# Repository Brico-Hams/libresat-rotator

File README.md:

<p align="center"><a href="https://bricohams.org">bricohams.org</a> · Anatol EA5KAO · Diego EA5JEF · Pedro Roca Molina</p>

# BricoHams · LibreSat rotators (LSR-1 and LSR-2)

**Light, cheap, open az/el rotators for amateur satellites.** Authors: Anatol EA5KAO, Diego EA5JEF, Pedro Roca Molina.

| | LSR-1 (portable) | LSR-2 (fixed station, heavy) |
|---|---|---|
| Design | printed cycloid actuators, Pi head, tripod or backpack | **replica of the SARCNET SARCTrac Mk4** (MIT files in [`third_party/sarctrac-mk4`](third_party/sarctrac-mk4)) |
| Drive | 2 × printed cycloid 25:1 + NEMA17 | 2 × NMRV30 worm gearbox 50:1 + NEMA23 23HS32-4004S, DM542T drivers at 48 V |
| Mass / cost | ≈ 2.3 kg, ≈ 150 € ([BOM](docs/BOM.md)) | **≈ 15.9 kg, ≈ 900 € (est.)**, generated by `calc/lsr2_mk4_bom.py` ([BOM_LSR2](docs/BOM_LSR2.md)) |
| Range | AZ 0–450°, EL 0–180° (flip) | AZ ±360° (cable wrap), EL −30…150° |
| Speed / load | pass planner < 16°/s | 12°/s; wind, gravity and speed limits in [LSR2_SIZING](docs/LSR2_SIZING.md) |
| Accuracy target | < 0.1° after calibration ([CALIBRATION](docs/CALIBRATION.md)) | same target, acceptance in [LSR2_ACCEPTANCE](docs/LSR2_ACCEPTANCE.md) |

**Build pipeline:** `make calc` (engineering checks and generated docs) · `make lsr2` (LSR-2 CAD, STL, laser DXF, drawings, wiring, BOM, technical figures) · `make render` (photoreal renders with Blender) · `make test` (firmware host tests and software tests).

**Credits:** SARCNET (SARCTrac Mk4 FreeCAD files under the MIT licence, the base of LSR-2; Mk5 published data; ideas from MK1), [SatNOGS Rotator v3](https://gitlab.com/librespacefoundation/satnogs/satnogs-rotator), [AntRunner](https://github.com/wuxx/AntRunner), [Sweep Dynamics](https://www.sweepdynamics.com/). Licences are listed in [Licences](#licences). Branding: [docs/BRANDING.md](docs/BRANDING.md).

---

## LSR-1: portable rotator

**A light, cheap, open az/el rotator for working amateur satellites in the field.**

LSR-1 starts from two open designs, the [SatNOGS Rotator v3](https://gitlab.com/librespacefoundation/satnogs/satnogs-rotator) and [AntRunner](https://github.com/wuxx/AntRunner). It uses the compact printed cycloidal actuators popularised by [Sweep Dynamics](https://www.sweepdynamics.com/) and puts a Raspberry Pi at the head. The goal is a rotator a radio amateur can print, solder and carry in a backpack. It sits on any photo or survey tripod and tracks a light antenna of the BigSignal **SpaceQuad** or Arrow class. It controls the radio's Doppler on a **Yaesu FTX-1** and keeps an **OpenGD77** radio in sync.

| | LSR-1 | AntRunner | SatNOGS Rotator v3 |
|---|---|---|---|
| Weight (rotator + controller) | **≈ 2.3 kg** (estimate, [BOM](docs/BOM.md)) | 3 kg | ≈ 5 kg |
| Parts cost | **≈ 150 €** with a Pi Zero 2 W | n/a (sold assembled) | 300–400 USD |
| Drive | 2 × printed cycloid 25:1 + NEMA17, steel pins, thin-section bearings | GRBL steppers, acrylic frame | worm gear 30:1 + GT2 belt, 20×20 extrusion |
| Range | AZ 0–450° (cable wrap), EL 0–180° (**flip**) | AZ 0–360°, EL 0–180° | AZ 0–360°, EL 0–90° |
| Position sensing | absolute EL (accelerometer), AZ index + saved position, **closed loop** with magnetic encoders | none (manual north, open loop) | encoders + endstops |
| Head computer | Pi Zero 2 W on the board: Wi-Fi AP, web UI, rotctld, **onboard tracking** | ESP32 GRBL + external PC/phone | external PC |
| Radio | **FTX-1 CAT Doppler** (direct or Hamlib), any Hamlib rig, **OpenGD77** clock/keps | via Gpredict | via Gpredict |
| Field power | 9–24 V: LiFePO4 / USB-C PD power bank; ≈ 4 W average | 12 V | 12 V |
| Mount | 3/8″ & 1/4″ photo, 5/8″ survey, 35 mm stand, 25–40 mm mast | U-bolt | custom |

## LSR-2: fixed-station rotator (SARCTrac Mk4 replica)

*LSR-2 on its mast, antennas at EL 30°. Render, not a photo (`make render`).*

LSR-2 is the heavy az/el rotator for a fixed station. It is a replica of the **SARCNET SARCTrac Mk4** and is built from the SARCNET FreeCAD files, which are under the MIT licence. The copy, its licence and its provenance are in [`third_party/sarctrac-mk4`](third_party/sarctrac-mk4). The details are in [LSR2_MK4](docs/LSR2_MK4.md).

**Hardware**

| Group | Parts |
|---|---|
| Drive | 2 × NMRV30 worm gearbox 50:1 (AZ and EL), 2 × NEMA23 23HS32-4004S (2.4 N·m, 4.0 A) |
| Electronics | 2 × DM542T drivers on 48 V (S-400-48 supply); 2 × XL7015 converters for 12 V and 5 V; controller (Wemos D1 Mini Pro in the original Mk4, see Control below); NJK-5002C Hall index sensors; mechanical end stops. Everything sits in a Deltron 483-0100 diecast housing. |
| Structure | 10 mm aluminium plate, saddle plates, brackets and platform; 16 mm corner blocks; 2 mm laser-cut aluminium cover and enclosure; 25 mm SHS lift arms |
| Bearings and mounting | stainless azimuth hub, thrust-bearing washer stack, U-bolts to the mast |

**Mass and cost.** The totals are ≈ 15.9 kg and ≈ 900 € (est., EU hobby suppliers 2026).

- The mass covers the rotator head, the electronics housing, the lift arms, the saddle and the fasteners. It leaves out the mast, the antennas, the cables and the indoor PSU. The cost does include the PSU and the motor cable.
- Made-part masses come from the CAD build report and bought-part masses from catalogue values. Laser and CNC prices are estimates until real quotes are in.
- Groups, processes and buy-in stock are in [BOM_LSR2](docs/BOM_LSR2.md) and [LSR2_MATERIALS](docs/LSR2_MATERIALS.md).

**Build files.**

- `make lsr2` (`LSR2_DESIGN=mk4`, the default) produces one STL and one STEP per part, plus the editable `cad/lsr2/LSR2_assembly.FCStd` and `cad/lsr2/LSR2_assembly.step.zip`. The STEP is zipped to stay under GitHub's 100 MB file limit.
- The laser-cut DXF files go to [`cnc/lsr2/laser/`](cnc/lsr2/laser).
- The fabrication drawings are the original SARCNET PDFs, listed in [docs/drawings](docs/drawings/).

**Control.** Our firmware, protocol and head software are shared with LSR-1 and run on the LSR-CTL RP2040 board, using the EXT_STEPDIR driver and the `lsr2` profile ([FIRMWARE](docs/FIRMWARE.md)). The original Mk4 uses a Wemos D1 Mini Pro with its own firmware. Whether we keep the RP2040 board or port our firmware to the Wemos is still open (O35 in [LSR2_MK4](docs/LSR2_MK4.md)). Both speak EasyComm II, so PstRotator, Gpredict, SatPC32 and Orbitron work, as does our rotctld server. Wiring: [LSR2_wiring.svg](docs/drawings/LSR2_wiring.svg).

### LSR-2 renders

*Head with the cover removed: the 10 mm plate carries both worm gearboxes and motors. The saddle and the lift arms take the antenna boom.*

*Exploded view: head, cover panels, saddle, lift arms and the mast clamp.*

*Elevation range: the saddle and lift arms at −30°, 45° and 150° about the EL axis.*

*The 2 mm laser-cut cover and enclosure panels (DXF in `cnc/lsr2/laser/`).*

**Technical views** (matplotlib drawings from the same STL files, colour = material or part type):

### Optional cast/CNC variant and earlier studies

The phase-11 design stays available as an optional variant (`LSR2_DESIGN=cast`). It is an open aluminium box with our own geometry from `cad/lsr2/*.py`, either sand-cast in A356 ([route A](docs/LSR2_ROUTE_A_CASTING.md)) or machined from slabs ([route B](docs/LSR2_ROUTE_B_CNC.md)). It uses 80:1 gearboxes and can take our own LSR-WG30 gearbox. Its drawings are in [docs/drawings/cast_variant](docs/drawings/cast_variant/). The Fusion layout is a study of the Mk5-style arrangement with our own dimensions ([LSR2_FUSION](docs/LSR2_FUSION.md)).

## What is in the box

| Folder | Contents |
|---|---|
| [`cad/`](cad) | LSR-1: OpenSCAD source of every printed part (`lsr.scad`, parameters in `lsr_params.scad`). LSR-2: `cad/lsr2/` FreeCAD build scripts (`build.py`, `mk4_build.py`, `mk4_params.py`), the assembly model and the zipped STEP |
| [`third_party/sarctrac-mk4/`](third_party/sarctrac-mk4) | SARCNET SARCTrac Mk4 FreeCAD files and drawings (MIT), with LICENSE, PROVENANCE and checksums |
| [`stl/`](stl) | Ready-to-print LSR-1 STL; LSR-2 STL per part in `stl/lsr2/` |
| [`cnc/`](cnc) | LSR-2 laser-cut DXF (`cnc/lsr2/laser/`) |
| [`hardware/`](hardware) | **LSR-CTL** controller board: KiCad 7 PCB generated by script, autorouted, DRC-clean, plus **Gerbers**, drill, BOM, pick-and-place and netlist in `hardware/fab/` |
| [`firmware/`](firmware) | RP2040 (Raspberry Pi Pico) firmware in C/C++ (Pico SDK): Easycomm II, closed loop, TMC2209 UART, IMU, GPS, LSR-2 EXT_STEPDIR profile, plus host unit tests |
| [`software/`](software) | Python head software for the Pi (`lsr`): tracker with pass planner, rotctld server, web UI, Doppler CAT (FTX-1, Hamlib), OpenGD77 tools, simulator and tests |
| [`calc/`](calc) | Engineering checks: LSR-1 cycloid, torque, speed, energy; LSR-2 sizing, materials and BOM |
| [`scripts/`](scripts) | Generators: BOM, drawings, wiring diagram, technical figures and Blender renders |
| [`docs/`](docs) | Every process, step by step (list below) |
| [`bom/`](bom) | Bills of materials with prices and masses |

## Documentation

**LSR-1 and shared**

1. [Design analysis](docs/DESIGN_ANALYSIS.md): what we took from SatNOGS v3, AntRunner, Sweep Dynamics and SARCNET, and what we changed and why.
2. [Engineering budget](docs/SIZING.md): torque, speed, pass dynamics and energy (generated by `calc/sizing.py`).
3. [Bill of materials](docs/BOM.md).
4. [Mechanical build](docs/MECHANICAL.md): printing, actuator assembly, base, head, antenna and tripod.
5. [Electronics](docs/ELECTRONICS.md): LSR-CTL board, pin map, soldering, harness, sensors and bring-up; LSR-2 drivers and power.
6. [Firmware](docs/FIRMWARE.md): build and flash, the command protocol, settings, referencing and the `lsr2` profile.
7. [Head software](docs/SOFTWARE.md): Pi install, web UI, Gpredict/Look4Sat/SatNOGS, FTX-1, Hamlib and OpenGD77.
8. [Power](docs/POWER.md): batteries, USB-C PD, protection and the energy budget.
9. [Calibration and field use](docs/FIELD_GUIDE.md): from the bag to the first QSO in 10 minutes. [Automatic calibration and pointing correction](docs/CALIBRATION.md): level, GPS, compass, Sun, index/backlash, pointing fit.
10. [Testing](docs/TESTING.md): unit, bench and acceptance tests with result sheets.
11. [Family architecture](docs/ARCHITECTURE.md): LSR-1 and LSR-2, the shared stack, phase status.

**LSR-2**

12. [SARCTrac Mk4 replica](docs/LSR2_MK4.md): credit and licence, parts by process, build, laser DXF, electronics, differences, open items.
13. [Engineering budget](docs/LSR2_SIZING.md): wind and gravity torques, bearings, mast, clamps, fixings, power, pointing error. Inputs in [LSR2_INPUTS](docs/LSR2_INPUTS.md).
14. [Materials and cost](docs/LSR2_MATERIALS.md): stock per material, nesting, waste and cost.
15. [Bill of materials](docs/BOM_LSR2.md): every made and bought part, with mass and cost totals.
16. [Assembly guide](docs/LSR2_ASSEMBLY.md): order following the SARCNET assembly drawings, fasteners and torques, cabling and corrosion protection.
17. [Tolerances](docs/LSR2_TOLERANCES.md) and [inspection sheet](docs/LSR2_INSPECTION.md) (generated from `cad/lsr2/tolerances.py`).
18. [Drawings](docs/drawings/): SARCNET PDFs, exploded view with BOM balloons, and the [wiring diagram](docs/drawings/LSR2_wiring.svg).
19. [Risk review](docs/LSR2_RISKS.md), [test plan](docs/LSR2_TEST_PLAN.md) and [acceptance checklist](docs/LSR2_ACCEPTANCE.md).
20. [Open items](docs/OPEN_ITEMS.md): everything that needs the real world (measurements, quotes, tests).
21. Optional cast/CNC variant: [design spec](docs/superpowers/specs/2026-11-16-lsr2-heavy-rotator-design.md) (historical), [route A casting](docs/LSR2_ROUTE_A_CASTING.md), [route B CNC](docs/LSR2_ROUTE_B_CNC.md), [Fusion layout](docs/LSR2_FUSION.md).

## Key ideas (LSR-1)

- **One actuator, printed twice.** A NEMA17 drives a 25:1 two-disc cycloidal reducer that runs on 26 steel dowel ring pins. The output runs in two thin-section 61810 bearings. It is 94 mm across and about 45 mm long plus the motor. The tooth profile is checked in `calc/cycloid_check.py`, with 0.13 mm minimum running clearance over a full cycle.
- **No endstops needed.**
  - Elevation is absolute: an accelerometer on the elevation stub measures gravity.
  - Azimuth comes back from the position saved in flash, checked against the motor encoder, or from a hall index magnet (`HOME`).
  - True north is found by **pointing at the Sun** with the printed sun sight: one button press.
- **Closed loop.** An AS5600 on each motor's rear shaft detects lost steps and re-synchronises the step counter.
- **Automatic calibration and pointing model (Phase 8).** `lsr calibrate level|compass|sun|sun-manual|index|all` uses GPS time and position, the Sun and the IMUs; `lsr pointing fit` fits north, horizon, tilt, non-perpendicularity, collimation, eccentricity and backlash terms and reports the residual RMS (goal < 0.1°). Optional closed loop with step-loss and stall detection, soft limits and safe states. See [Calibration](docs/CALIBRATION.md); the ideas follow SARCNET MK1 and Rotator7.
- **Flip and cable-wrap planner.** Overhead passes need more than 50°/s of azimuth with a plain az/el rotator. The planner instead chooses between normal, over-the-top (elevation 0–180°) and wrap-shifted trajectories. In a one-week simulation of 156 passes, every pass stayed under 16°/s with less than 0.7° pointing error ([SIZING](docs/SIZING.md)).
- **The Pi is the rotator head.** It runs its own Wi-Fi hotspot, a mobile web UI, offline TLEs, and a GPS position and clock. Its `rotctld` on port 4533 accepts Gpredict, Look4Sat, SatNOGS or any Hamlib client.
- **Doppler done right.** FM satellites are corrected on both uplink and downlink. Linear transponders follow the RX knob: tune the downlink and the uplink follows, inverting or not. The FTX-1 runs MAIN as RX and SUB as TX, with no hardware split.

## Quick start

```bash
make            # STL + renders, PCB fab outputs, firmware .uf2, unit tests, engineering docs
make test       # firmware host tests + software tests only
cd software && pip install . && lsr run --sim    # web UI on http://localhost:8080 with a simulated rotator
```

Requirements: OpenSCAD, KiCad 7, Java 17 (Freerouting, only to re-route the PCB), the ARM GCC toolchain with Pico SDK 2.x, and Python 3.9+. LSR-2 also needs FreeCAD 1.x (`freecadcmd`) and, for renders, Blender 5.x. See each document for details.

## Status and safety

This is a complete, reviewed design. **Neither rotator has yet been built and measured as a whole.** The simulations, unit tests, DRC and kinematic checks pass. LSR-2 prices are estimates, and its target firmware build and bench tests are still open ([OPEN_ITEMS](docs/OPEN_ITEMS.md)). Before you order boards, check the items marked **VERIFY** in the documents:

- the TMC2209 module pinout;
- the AP63205 pinout;
- the FTX-1 `FB` command and CAT tone syntax;
- OpenGD77 keps upload, which is experimental and makes a backup first.

Satellites change status often. Check the [AMSAT status page](https://www.amsat.org/status/) before a pass.

## Licences

- Hardware (CAD, PCB): **CERN-OHL-S-2.0**.
- `third_party/sarctrac-mk4`: **MIT** (SARCNET; SARCTrac Mk4 FreeCAD files, see its LICENSE and PROVENANCE.md).
- Firmware and software: **GPL-3.0-or-later**.
- Documentation and images: **CC BY-SA 4.0**.

See [LICENSE](LICENSE). Hamlib, Gpredict, OpenGD77, SatNOGS and AntRunner are the work of their respective authors, and LSR-1 only talks to them through their public interfaces.

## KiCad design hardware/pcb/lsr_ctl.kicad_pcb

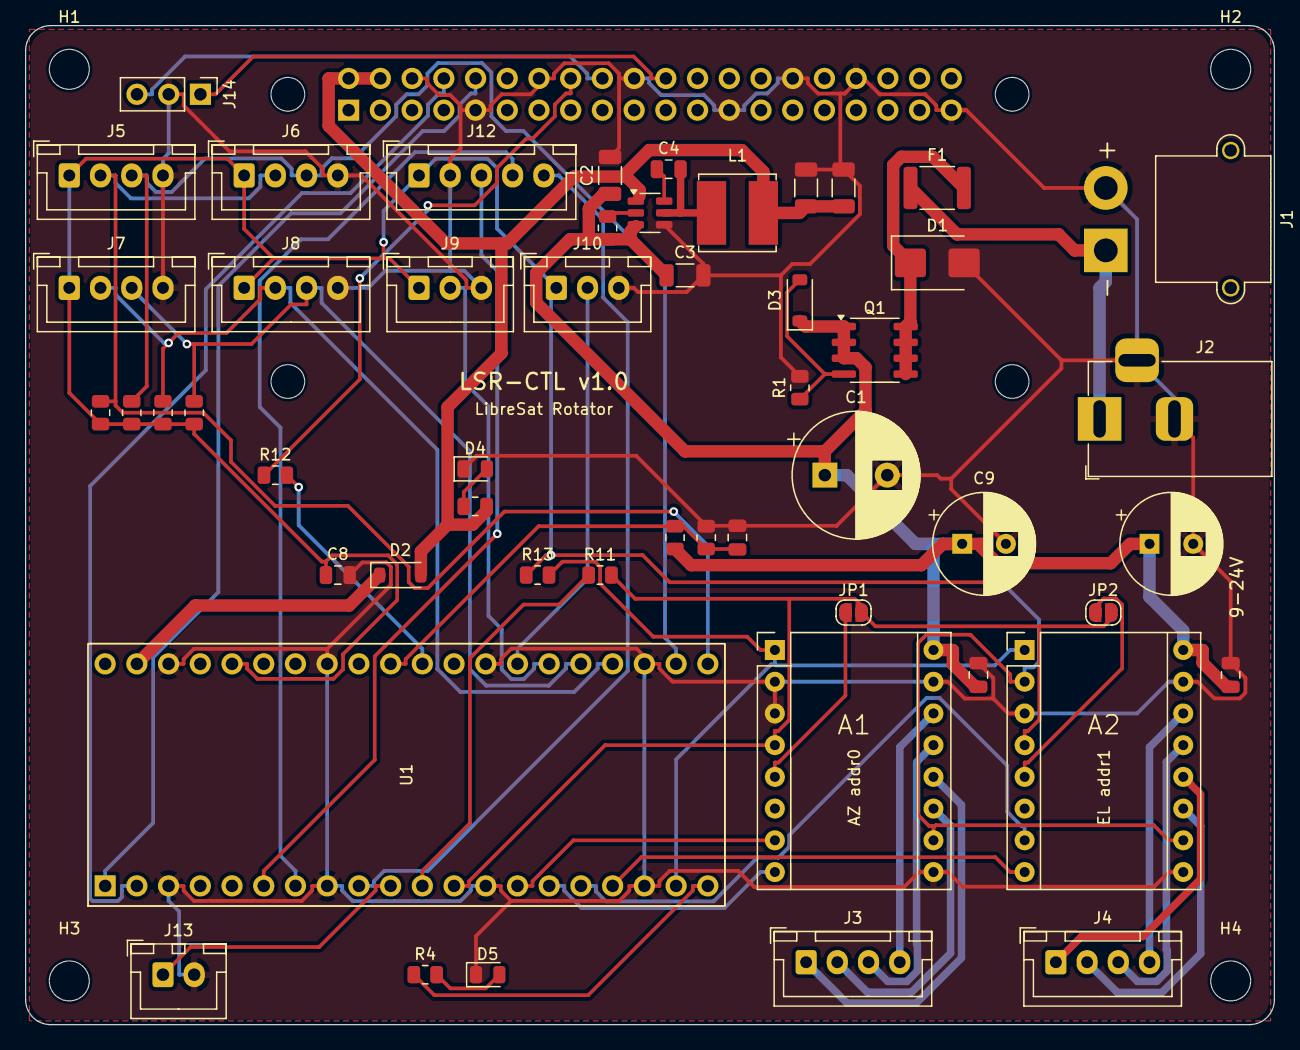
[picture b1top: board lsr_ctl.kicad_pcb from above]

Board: 2 copper layers, 100.0 x 80.0 mm, 61 parts (1 on the bottom side), 48 nets.

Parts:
A1: TMC2209 AZ (addr 0); Pololu_Breakout-16_15.2x20.3mm
A2: TMC2209 EL (addr 1); Pololu_Breakout-16_15.2x20.3mm
C1: 470uF 35V; CP_Radial_D10.0mm_P5.00mm
C2, C3: 10uF 50V; C_1206_3216Metric
C4, C7, C11, C12: 100nF; C_0805_2012Metric
C5, C6: 22uF 10V; C_1206_3216Metric
C8: 10uF; C_0805_2012Metric
C9, C10: 100uF 35V; CP_Radial_D8.0mm_P3.50mm
D1: SMBJ24A; D_SMB
D2: B5819W (5V->VSYS); D_SOD-123
D3: BZT52C12 (12V); D_SOD-123
D4: green PWR; LED_0805_2012Metric
D5: blue STATUS; LED_0805_2012Metric
F1: PTC 2.5A hold (1812L250); Fuse_1812_4532Metric
H1, H2, H3, H4: M3; MountingHole_3.2mm_M3
H5, H6, H7, H8: M2.5 Pi; MountingHole_2.7mm_M2.5
J1: XT30 9-24V; AMASS_XT30PW-M_1x02_P2.50mm_Horizontal
J2: 5.5x2.1 9-24V; BarrelJack_Horizontal
J3: MOTOR AZ; JST_XH_B4B-XH-A_1x04_P2.50mm_Vertical
J4: MOTOR EL; JST_XH_B4B-XH-A_1x04_P2.50mm_Vertical
J5: ENC AZ (AS5600); JST_XH_B4B-XH-A_1x04_P2.50mm_Vertical
J6: IMU BASE; JST_XH_B4B-XH-A_1x04_P2.50mm_Vertical
J7: ENC EL (AS5600); JST_XH_B4B-XH-A_1x04_P2.50mm_Vertical
J8: IMU EL (boom); JST_XH_B4B-XH-A_1x04_P2.50mm_Vertical
J9: HALL AZ; JST_XH_B3B-XH-A_1x03_P2.50mm_Vertical
J10: HALL/LIM EL; JST_XH_B3B-XH-A_1x03_P2.50mm_Vertical
J11: Pi Zero 2 W; PinSocket_2x20_P2.54mm_Vertical
J12: GPS; JST_XH_B5B-XH-A_1x05_P2.50mm_Vertical
J13: PARK/STOP; JST_XH_B2B-XH-A_1x02_P2.50mm_Vertical
J14: SWD from Pi; PinHeader_1x03_P2.54mm_Vertical
JP1: PDN pin5 AZ; SolderJumper-2_P1.3mm_Open_RoundedPad1.0x1.5mm
JP2: PDN pin5 EL; SolderJumper-2_P1.3mm_Open_RoundedPad1.0x1.5mm
L1: 6.8uH 3A (SRN6045TA-6R8M); L_Bourns_SRN6045TA
Q1: AO4407A P-MOSFET; SOIC-8_3.9x4.9mm_P1.27mm
R1, R6, R13: 10k; R_0805_2012Metric
R2, R5: 100k; R_0805_2012Metric
R3: 2k2; R_0805_2012Metric
R4, R11, R12: 1k; R_0805_2012Metric
R7, R8, R9, R10: 4k7; R_0805_2012Metric
U1: Raspberry Pi Pico; RaspberryPi_Pico_THT
U2: AP63205WU; TSOT-23-6

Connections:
+3V3: A1.10, A2.2, A2.10, C8.1, J5.1, J6.1, J7.1, J8.1, J9.1, J10.1, J12.1, R7.1, R8.1, R9.1, R10.1, R13.1, U1.36
+5V: C5.1, C6.1, D2.2, J11.2, J11.4, L1.2, R3.2, U2.1
BTN: J13.1, U1.10
BUCK_BST: C4.1, U2.6
BUCK_EN: R2.2, U2.2
BUCK_SW: C4.2, L1.1, U2.5
DIR_AZ: A1.8, U1.15
DIR_EL: A2.8, U1.17
GND: A1.2, A1.3, A1.9, A1.15, A2.3, A2.9, A2.15, C1.2, C2.2, C3.2, C5.2, C6.2, C7.2, C8.2, C9.2, C10.2, C11.2, C12.2, D1.2, D4.1, D5.1, J1.2, J2.2, J2.3, J5.4, J6.4, J7.4, J8.4, J9.3, J10.3, J11.6, J11.9, J11.14, J11.20, J11.25, J11.30, J11.34, J11.39, J12.2, J13.2, J14.2, R1.2, R6.2, U1.3, U1.8, U1.13, U1.18, U1.23, U1.28, U1.33, U1.38, U2.4
GPS_PPS: J12.5, U1.9
GPS_RX: J12.3, U1.6
GPS_TX: J12.4, U1.7
HALL_AZ: J9.2, U1.26
HALL_EL: J10.2, U1.27
LED: R4.1, U1.20
LED_A: D5.2, R4.2
LED_PWR_A: D4.2, R3.1
MAZ_1A: A1.12, J3.1
MAZ_1B: A1.11, J3.2
MAZ_2A: A1.13, J3.3
MAZ_2B: A1.14, J3.4
MEL_1A: A2.12, J4.1
MEL_1B: A2.11, J4.2
MEL_2A: A2.13, J4.3
MEL_2B: A2.14, J4.4
NEN: A1.1, A2.1, R13.2, U1.19
PDN2_MAZ: A1.5, JP1.1
PDN2_MEL: A2.5, JP2.1
PI_RESET: J11.16, R12.1
PI_RX: J11.10, U1.1
PI_SWCLK: J11.22, J14.1
PI_SWDIO: J11.18, J14.3
PI_TX: J11.8, U1.2
QGATE: D3.2, Q1.4, R1.1
RUN: R12.2, U1.30
SCL0: J5.3, J6.3, R8.2, U1.22
SCL1: J7.3, J8.3, R10.2, U1.25
SDA0: J5.2, J6.2, R7.2, U1.21
SDA1: J7.2, J8.2, R9.2, U1.24
STEP_AZ: A1.7, U1.14
STEP_EL: A2.7, U1.16
TMC_TX: R11.1, U1.11
TMC_UART: A1.4, A2.4, JP1.2, JP2.2, R11.2, U1.12
VIN_F: D1.1, F1.2, Q1.5, Q1.6, Q1.7, Q1.8
VIN_RAW: F1.1, J1.1, J2.1
VM: A1.16, A2.16, C1.1, C2.1, C3.1, C9.1, C10.1, C11.1, C12.1, D3.1, Q1.1, Q1.2, Q1.3, R2.1, R5.1, U2.3
VSENSE: C7.1, R5.2, R6.1, U1.31
VSYS: D2.1, U1.39

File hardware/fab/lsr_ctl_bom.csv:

qty,refs,value,footprint,note
1,A1,TMC2209 AZ (addr 0),Pololu_Breakout-16_15.2x20.3mm,"TMC2209 StepStick (BTT / FYSETC, UART) + 2x 1x8 female headers + heatsink"
1,A2,TMC2209 EL (addr 1),Pololu_Breakout-16_15.2x20.3mm,"TMC2209 StepStick (BTT / FYSETC, UART) + 2x 1x8 female headers + heatsink"
1,C1,470uF 35V,CP_Radial_D10.0mm_P5.00mm,
2,C2 C3,10uF 50V,C_1206_3216Metric,
4,C4 C7 C11 C12,100nF,C_0805_2012Metric,
2,C5 C6,22uF 10V,C_1206_3216Metric,
1,C8,10uF,C_0805_2012Metric,
2,C9 C10,100uF 35V,CP_Radial_D8.0mm_P3.50mm,
1,D1,SMBJ24A,D_SMB,
1,D2,B5819W (5V->VSYS),D_SOD-123,
1,D3,BZT52C12 (12V),D_SOD-123,
1,D4,green PWR,LED_0805_2012Metric,
1,D5,blue STATUS,LED_0805_2012Metric,
1,F1,PTC 2.5A hold (1812L250),Fuse_1812_4532Metric,
1,JP1,PDN pin5 AZ,SolderJumper-2_P1.3mm_Open_RoundedPad1.0x1.5mm,
1,J1,XT30 9-24V,AMASS_XT30PW-M_1x02_P2.50mm_Horizontal,"AMASS XT30PW-M (male, PCB right-angle)"
1,JP2,PDN pin5 EL,SolderJumper-2_P1.3mm_Open_RoundedPad1.0x1.5mm,
1,J2,5.5x2.1 9-24V,BarrelJack_Horizontal,5.5 x 2.1 mm DC jack
1,J3,MOTOR AZ,JST_XH_B4B-XH-A_1x04_P2.50mm_Vertical,
1,J4,MOTOR EL,JST_XH_B4B-XH-A_1x04_P2.50mm_Vertical,
1,J5,ENC AZ (AS5600),JST_XH_B4B-XH-A_1x04_P2.50mm_Vertical,
1,J6,IMU BASE,JST_XH_B4B-XH-A_1x04_P2.50mm_Vertical,
1,J7,ENC EL (AS5600),JST_XH_B4B-XH-A_1x04_P2.50mm_Vertical,
1,J8,IMU EL (boom),JST_XH_B4B-XH-A_1x04_P2.50mm_Vertical,
1,J9,HALL AZ,JST_XH_B3B-XH-A_1x03_P2.50mm_Vertical,
1,J10,HALL/LIM EL,JST_XH_B3B-XH-A_1x03_P2.50mm_Vertical,
1,J11,Pi Zero 2 W,PinSocket_2x20_P2.54mm_Vertical,"2x20 female socket, 8.5 mm (mounted on the BOTTOM side)"
1,J12,GPS,JST_XH_B5B-XH-A_1x05_P2.50mm_Vertical,
1,J13,PARK/STOP,JST_XH_B2B-XH-A_1x02_P2.50mm_Vertical,
1,J14,SWD from Pi,PinHeader_1x03_P2.54mm_Vertical,
1,L1,6.8uH 3A (SRN6045TA-6R8M),L_Bourns_SRN6045TA,
1,Q1,AO4407A P-MOSFET,SOIC-8_3.9x4.9mm_P1.27mm,
3,R1 R6 R13,10k,R_0805_2012Metric,
2,R2 R5,100k,R_0805_2012Metric,
1,R3,2k2,R_0805_2012Metric,
3,R4 R11 R12,1k,R_0805_2012Metric,
4,R7 R8 R9 R10,4k7,R_0805_2012Metric,
1,U1,Raspberry Pi Pico,RaspberryPi_Pico_THT,Raspberry Pi Pico (or Pico W / Pico 2) + 2x 1x20 headers
1,U2,AP63205WU,TSOT-23-6,

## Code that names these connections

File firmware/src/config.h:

// LibreSat Rotator firmware — board pin map and compile-time defaults (LSR-CTL v1.0)
#pragma once

// ---------------- build selection (CMake: -DLSR_MODEL=1|2, -DLSR_DRIVER=TMC2209_UART|EXT_STEPDIR)
#define TMC2209_UART 1             // LSR-1: internal TMC2209 on UART, STEP/DIR on the board
#define EXT_STEPDIR  2             // LSR-2: external DM542 / TMC5160 in STEP/DIR mode, no UART calls
#ifndef LSR_MODEL
#define LSR_MODEL 1
#endif
#ifndef LSR_DRIVER
#if LSR_MODEL == 2
#define LSR_DRIVER EXT_STEPDIR
#else
#define LSR_DRIVER TMC2209_UART
#endif
#endif

#if LSR_MODEL == 2
#define FW_NAME     "LSR-2"
#else
#define FW_NAME     "LSR-1"
#endif
#define FW_VERSION  "1.1.0"

// ---------------- pins (Raspberry Pi Pico GPIO numbers)
#define PIN_PI_TX        0    // UART0 TX -> Pi GPIO15 (RXD)
#define PIN_PI_RX        1    // UART0 RX <- Pi GPIO14 (TXD)
#define PIN_GPS_TX       4    // UART1 TX -> GPS RX
#define PIN_GPS_RX       5    // UART1 RX <- GPS TX
#define PIN_GPS_PPS      6
#define PIN_BTN          7    // PARK/STOP button to GND
#define PIN_TMC_TX       8    // PIO UART TX (through 1k) -> PDN_UART
#define PIN_TMC_RX       9    // PIO UART RX  <- PDN_UART
#define PIN_STEP_AZ     10
#define PIN_DIR_AZ      11
#define PIN_STEP_EL     12
#define PIN_DIR_EL      13
#define PIN_NEN         14    // driver enable, active low (10k pull-up on board)
#define PIN_LED         15
#define PIN_SDA0        16    // I2C0: AZ encoder + base IMU
#define PIN_SCL0        17
#define PIN_SDA1        18    // I2C1: EL encoder + boom IMU
#define PIN_SCL1        19
#define PIN_HALL_AZ     20    // AZ index (active low). LSR-1: DRV5032FB / AH1806 at 3.3 V. LSR-2 Mk4: NJK-5002C NPN Hall switch (12 V supply, open collector)
#define PIN_HALL_EL     21    // EL index. LSR-2 Mk4: NJK-5002C; LSR-1: optional index / limit
#define PIN_PWRFAIL     22    // LSR-2: 48 V opto-isolated power-loss detect (high = 48 V gone), see PWR_* below
#define PIN_VSENSE      26    // ADC0: VM / 11
#define ADC_VSENSE       0
#define PIN_ONBOARD_LED 25    // plain Pico; Pico W uses the CYW43 LED (not driven)

// EXT_STEPDIR: STEP/DIR stay on GPIO10..13; one enable per axis on the free pins GPIO2/GPIO3.
// PIN_NEN (GPIO14) is not driven by the drivers in this mode.
#define PIN_EN_AZ        2
#define PIN_EN_EL        3
#define EXT_STEP_ACTIVE  1    // pin level while the STEP pulse is high (after the buffer/opto stage)
#define EXT_DIR_POS_LEVEL 1   // DIR pin level for +1
#define EXT_EN_ACTIVE    0    // DM542 ENA is often active-low: enabled = low, disabled = high (VERIFY)

// LSR-2 index. Mk4 replica: NJK-5002C NPN Hall switch (SARCNET Hall Effect Switch) per axis, magnet on the moving part; the open-collector output
// pulls the pin LOW while the magnet is in range (active low = IDX_SLOT_LEVEL 0). The sensor runs on 12 V (XL7015), so the output is pulled up to
// 3.3 V on the RP2040 side only (the NPN open collector never drives the pin high: no 5 V/12 V on the GPIO; add a 10 k series resistor + 3.3 V
// pull-up on the controller board). The earlier phase-11 design used a photo-interrupter + slotted disc with the same logic level.
// Mechanical end stops (microswitches on the saddle, SARCNET "End Stop") are a fail-safe independent of the firmware: wired normally closed in
// series with the driver enable (ENA) of the axis, so a pressed switch or a cut wire disables that driver in hardware. No GPIO is needed;
// to also read them add a spare input with the same pull-up logic (the firmware limits and the bumpers act first). LSR-1 keeps its hall sensor.
#define IDX_SLOT_LEVEL   0
// LSR-2 power-loss detect: the opto transistor pulls PIN_PWRFAIL low while 48 V is present. On loss the firmware stops the
// motors and saves the position to flash (bulk capacitance on the 48 V rail keeps the 5 V buck alive for the ~60 ms write).
// Armed only after 48 V has been seen once since boot, so a bench build without the circuit still works.
#define PWR_LOSS_LEVEL   1

// ---------------- serial
#if LSR_MODEL == 2
#define PI_BAUD       9600       // EasyComm II 9600 8N1: what SARCTrac Mk5 trackers (PstRotator, Gpredict, SatPC32, Orbitron) expect
#else
#define PI_BAUD     115200
#endif
#define GPS_BAUD      9600
#define TMC_BAUD    115200

// ---------------- motion defaults (all overridable with XC key=value, stored in flash)
// ratio, microsteps, ranges, vmax and acc per axis come from the model profile (core.cpp: lsr_model()).
#define DEF_FULLSTEPS   200
#define DEF_IRUN_MA     900        // TMC2209 RMS run current
#define DEF_IHOLD_PCT    35        // hold current (% of run)
#define DEF_DEADBAND     0.05f     // deg

#define STEP_ISR_HZ   25000        // step generator tick
#define PLAN_HZ         500        // planner / encoder loop
#define IMU_HZ           50

// ---------------- sensors
#define AS5600_ADDR   0x36
#define MPU_ADDR      0x68
#define ENC_CPR       4096

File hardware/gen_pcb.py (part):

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    # ---------------- stepper drivers (TMC2209 StepStick, UART addr 0 = AZ, 1 = EL)
    'A1': ('Module', 'Pololu_Breakout-16_15.2x20.3mm', 'TMC2209 AZ (addr 0)', 60.0, 50.0, 0, driver('GND', 'STEP_AZ', 'DIR_AZ', 'MAZ'), 'F'),
    'A2': ('Module', 'Pololu_Breakout-16_15.2x20.3mm', 'TMC2209 EL (addr 1)', 80.0, 50.0, 0, driver('+3V3', 'STEP_EL', 'DIR_EL', 'MEL'), 'F'),
    'JP1': ('Jumper', 'SolderJumper-2_P1.3mm_Open_RoundedPad1.0x1.5mm', 'PDN pin5 AZ', 66.3, 47.0, 0, {'1': 'PDN2_MAZ', '2': 'TMC_UART'}, 'F'),
    'JP2': ('Jumper', 'SolderJumper-2_P1.3mm_Open_RoundedPad1.0x1.5mm', 'PDN pin5 EL', 86.3, 47.0, 0, {'1': 'PDN2_MEL', '2': 'TMC_UART'}, 'F'),
    'C9': ('Capacitor_THT', 'CP_Radial_D8.0mm_P3.50mm', '100uF 35V', 75.0, 41.5, 0, {'1': 'VM', '2': 'GND'}, 'F'),
    'C10': ('Capacitor_THT', 'CP_Radial_D8.0mm_P3.50mm', '100uF 35V', 90.0, 41.5, 0, {'1': 'VM', '2': 'GND'}, 'F'),
    'C11': C0805 + ('100nF', 76.3, 52.0, 90, {'1': 'VM', '2': 'GND'}, 'F'),
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

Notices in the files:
hardware/pcb/lsr_ctl.kicad_pcb:
CERN-OHL-S v2
